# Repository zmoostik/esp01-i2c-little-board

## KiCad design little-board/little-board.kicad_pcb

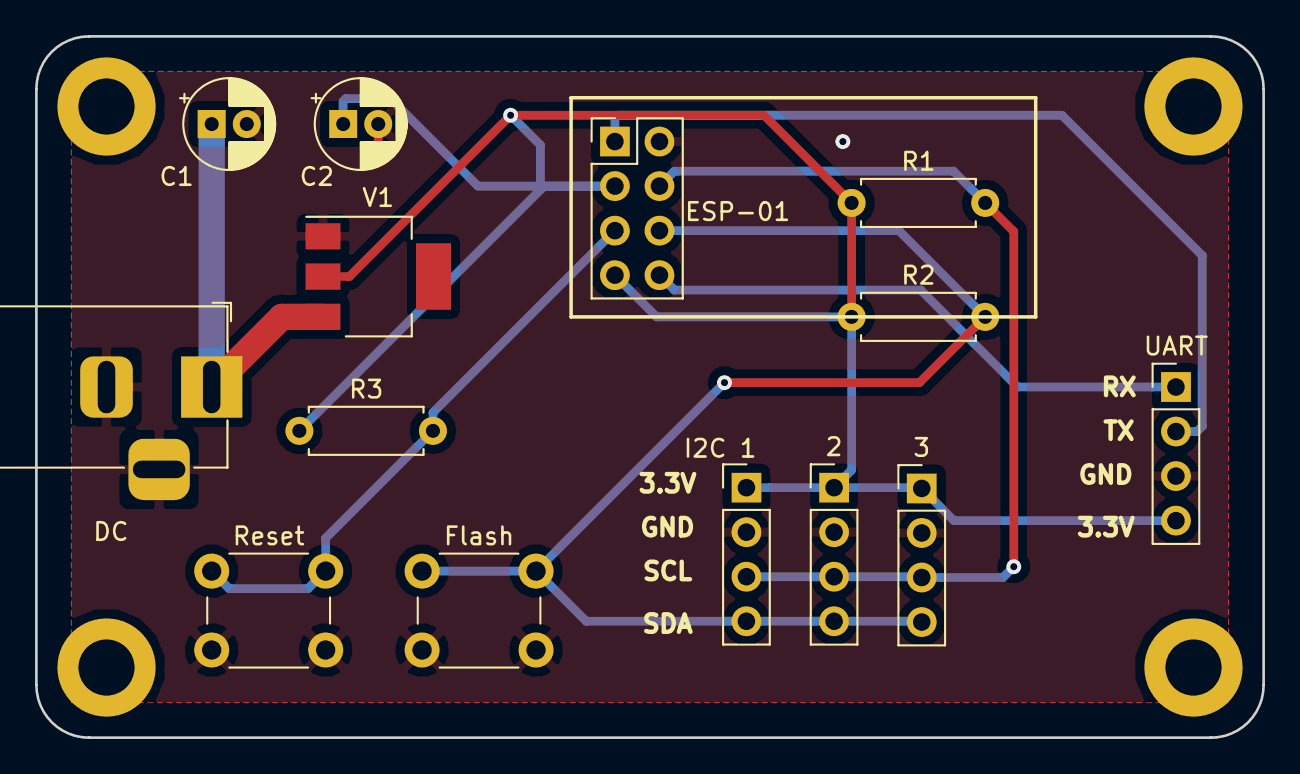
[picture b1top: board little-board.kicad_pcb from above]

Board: 2 copper layers, 70.0 x 40.0 mm, 14 parts (0 on the bottom side), 8 nets.

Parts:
2, 3: I2C_SENS; PinHeader_1x04_P2.54mm_Vertical
C1: 100nF; CP_Radial_D5.0mm_P2.00mm
C2: 10uF; CP_Radial_D5.0mm_P2.00mm
DC: DC Jack; BarrelJack_Horizontal
ESP-01: ESP-01v090; PinHeader_2x04_P2.54mm_Vertical
Flash: SW_DIP_x01; SW_PUSH_6mm_H5mm
I2C 1: I2C_SENS; PinHeader_1x04_P2.54mm_Vertical
R1, R2: 4,7K; R_Axial_DIN0207_L6.3mm_D2.5mm_P7.62mm_Horizontal
R3: 10K; R_Axial_DIN0207_L6.3mm_D2.5mm_P7.62mm_Horizontal
Reset: SW_DIP_x01; SW_PUSH_6mm_H5mm
UART: Conn_01x04; PinHeader_1x04_P2.54mm_Vertical
V1: LD1117S33TR; SOT-223

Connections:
+3V3: 2.1, 3.1, C2.1, ESP-01.3, ESP-01.7, I2C 1.1, R1.1, R2.1, R3.1, UART.4, V1.2
+12V: C1.1, DC.1, V1.3
/RX: ESP-01.8, UART.1
/SCL: 2.3, 3.3, ESP-01.4, I2C 1.3, R1.2
/SDA: 2.4, 3.4, ESP-01.6, Flash.1, I2C 1.4, R2.2
/TX: ESP-01.1, UART.2
GND: 2.2, 3.2, C1.2, C2.2, DC.2, DC.3, ESP-01.2, Flash.2, I2C 1.2, Reset.2, UART.3, V1.1
unnamed: ESP-01.5, R3.2, Reset.1

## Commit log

2018-10-21 * first release
2018-10-21 * reliquat
